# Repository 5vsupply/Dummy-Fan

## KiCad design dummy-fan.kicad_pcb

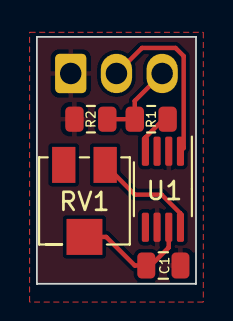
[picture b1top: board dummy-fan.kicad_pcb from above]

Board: 2 copper layers, 8.8 x 13.7 mm, 6 parts (1 on the bottom side), 6 nets.

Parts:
C1: 1uF; C_0805_2012Metric
J1: Conn_01x03; Molex_KK-254_AE-6410-03A_1x03_P2.54mm_Vertical
R1: 8.7k; R_0805_2012Metric
R2: 3.3k; R_0805_2012Metric
RV1: 10k; Potentiometer_Bourns_3224J_Horizontal
U1: BD9555FVM; MSOP-8_3x3mm_P0.65mm

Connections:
+12V: J1.2, U1.1 (VCC)
/TACH: J1.3, R1.2, R2.1
GND: C1.2, J1.1, R2.2, U1.2 (DCENB), U1.6 (GND)
unnamed: C1.1, RV1.2, U1.7 (CRT)
unnamed: RV1.3, U1.8 (DIS)
unnamed: R1.1, U1.4 (OUT)

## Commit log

2022-04-22 init
